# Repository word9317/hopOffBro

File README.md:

# Hop Off Bro
An alarm clock built for standing desk workers, telling you to switch from sitting to standing or to just hop off!

## Features:
 - 3 Cherry MX switches for input
 - 2.25 in TFT screen
 - LEDs because who doesnt want RGB!
 - Firmware made using PlatformIO for modularity

## Gallery:

## BOM:
- 1x Seeed XIAO ESP32C3
- 3x MX-Style Keyboard switches
- 3x White DSA keycaps
- 4x SK6812 LEDs
- 2.54 mm 8 male pin header
- 8x 20cm Female-Female Jumper wires
- 8x M3x5x4 Heatset Inserts
- 4x M3x8mm Screws
- 4x M3x16mm Screws
- 1x 3.3V Piezo Buzzer

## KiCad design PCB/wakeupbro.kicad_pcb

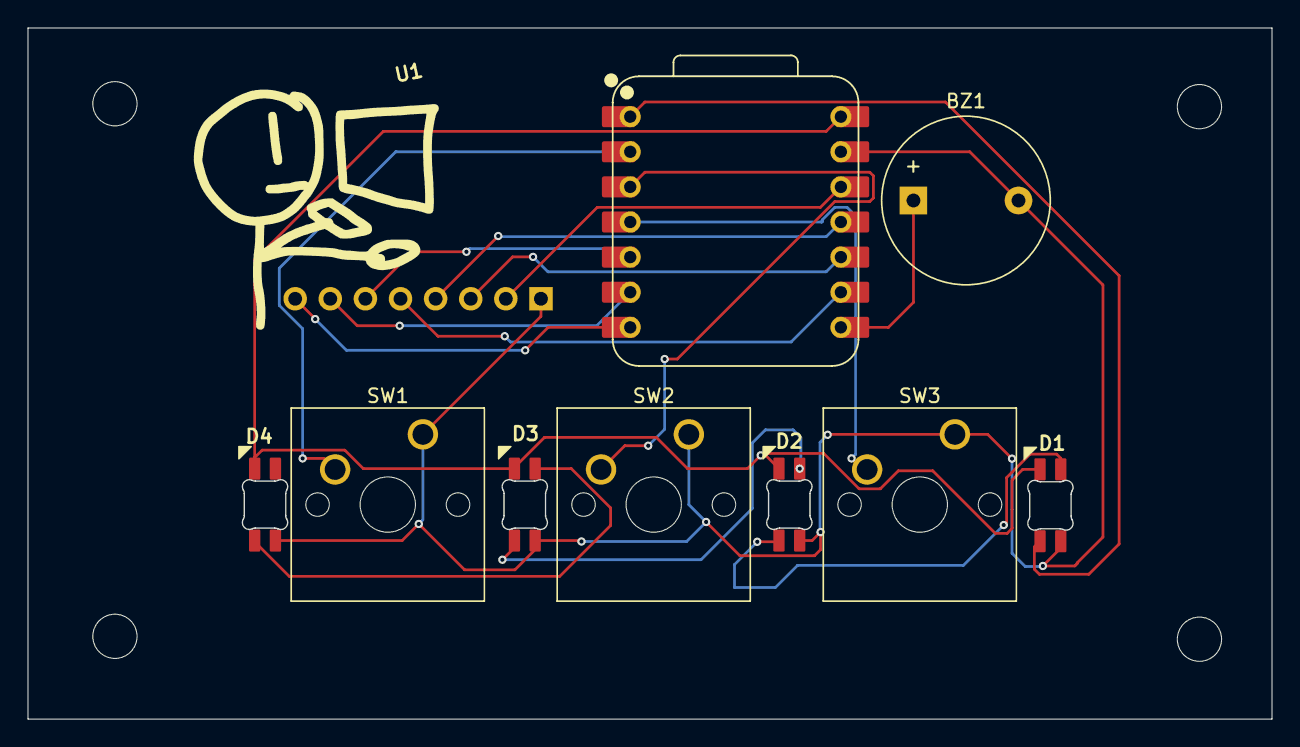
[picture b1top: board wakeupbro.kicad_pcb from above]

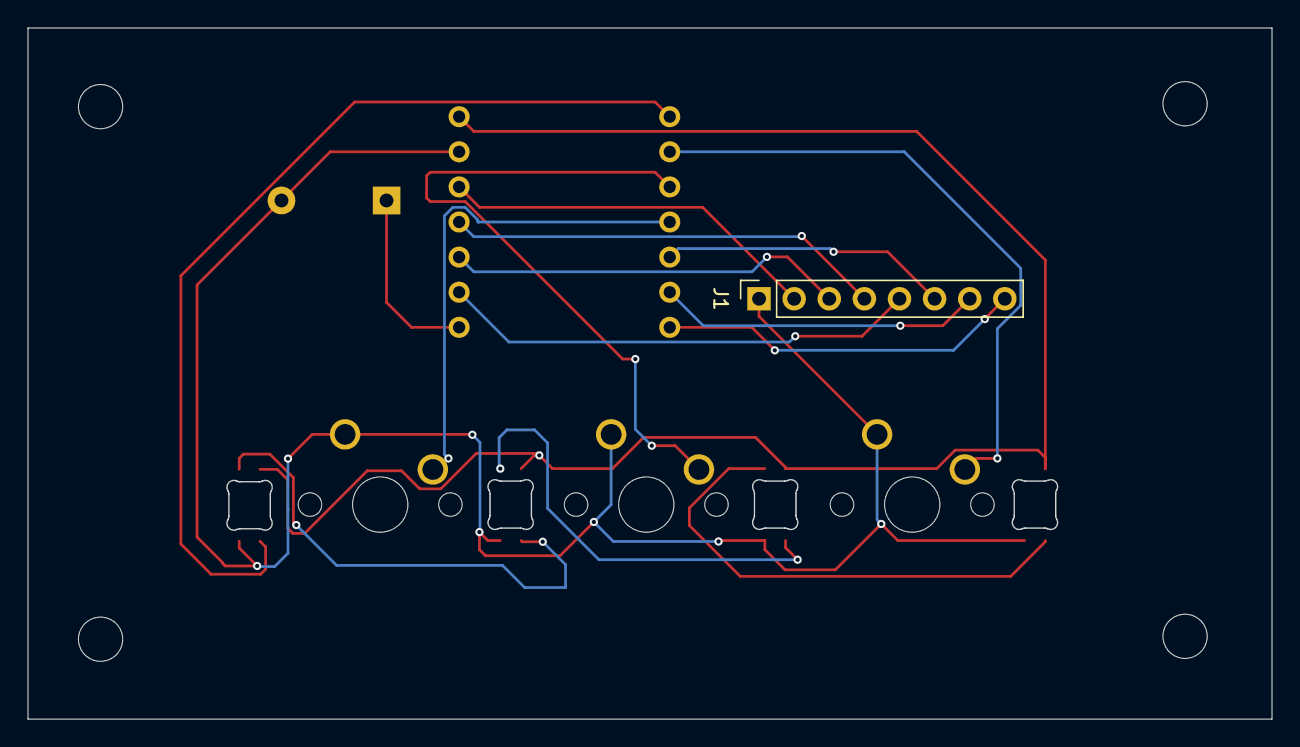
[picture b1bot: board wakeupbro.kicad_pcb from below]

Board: 2 copper layers, 90.0 x 50.0 mm, 14 parts (5 on the bottom side), 17 nets.

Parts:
BZ1: Buzzer; Buzzer_12x9.5RM7.6
D1, D2, D3, D4: SK6812MINI-E; SK6812MINI-E_fixed
H1, H2, H3, H4: MountingHole; MountingHole_3.2mm_M3
J1: Conn_01x08_Pin; PinSocket_1x08_P2.54mm_Vertical
SW1, SW2, SW3: SW_Push; SW_Cherry_MX_1.00u_PCB
U1: XIAO-ESP32-C3-SMD; XIAO-ESP32-C3-DIP

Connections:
+3V3: J1.2, U1.12 (3V3_OUT)
+5V: D1.3 (VDD), D2.3 (VDD), D3.3 (VDD), D4.3 (VDD), U1.14 (VBUS)
BL: J1.8, U1.7 (D6)
CS: J1.7, U1.6 (D5)
DC: J1.6, U1.5 (D4)
DIN: D1.2 (DIN), U1.1 (D0)
GND: BZ1.2 (-), D1.1 (VSS), D2.1 (VSS), D3.1 (VSS), D4.1 (VSS), J1.1, SW1.1, SW2.1, SW3.1, U1.13 (GND)
unnamed: BZ1.1 (+), U1.8 (D7)
unnamed: D1.4 (DOUT), D2.2 (DIN)
unnamed: D2.4 (DOUT), D3.2 (DIN)
unnamed: D3.4 (DOUT), D4.2 (DIN)
RST: J1.5, U1.9 (D8)
SCL: J1.3, U1.10 (D9/BOOT)
SDA: J1.4, U1.11 (D10)
SW1: SW1.2, U1.2 (D1)
SW2: SW2.2, U1.3 (D2)
SW3: SW3.2, U1.4 (D3)
